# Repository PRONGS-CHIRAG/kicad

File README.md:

# KiCAD Mitos

Natural-language batch editing for KiCAD. You select components, describe the change in plain
language, review a structured action plan, approve it, and the change is executed, verified with
KiCAD's own ERC and automatically rolled back if it fails verification.

Supported connection patterns: **I2C**, **SPI**, **UART**, a single **GPIO** link and a
**power-only** hookup. A protocol is a data table of per-signal pin aliases, named separately
for the controller and the peripheral — which is how UART's TX/RX crossover falls out with no
special case. All of them decompose into the same three action types.

## How it works

```
read project -> plan (rules or LLM) -> preview + approve -> checkpoint
             -> execute -> re-read + ERC -> deterministic decision -> accept | restore
```

- The LLM (optional) only *proposes* structured actions. It never decides whether a change is accepted.
- The accept/reject decision is deterministic and based on the real project: expected connections,
  supporting components, protected objects, unauthorized changes and new critical ERC violations.
- ERC is compared violation-by-violation against a baseline, not by counting, so pre-existing
  violations are never blamed on the change and a "swapped" violation is still detected.
- DRC runs too when the project has a board, including KiCAD's schematic-parity check, and it is a
  real gate for any run that wrote the board — which a schematic edit does, because the board is
  synced to match. The one carve-out is unconnected items whose every net that sync touched: a synced
  board is unrouted by design, so those are pending work, not a regression. An unconnected item on any
  other net still rejects, so severed copper cannot slip through.
- The DRC baseline is the union of a couple of passes, because KiCAD's own DRC is not deterministic:
  on a byte-identical board it intermittently reports one or two fewer clearance violations. Whichever
  run became the baseline would otherwise decide whether a later, normal run looked like it introduced
  errors, which rejected valid work about one time in twenty.
- The file-level diff is snapshotted straight after execution, before ERC runs, because `kicad-cli`
  rewrites project files as a side effect. Only the schematic may change; a touched `.kicad_pro` or
  symbol library is an unauthorized change.
- Every run is transactional: the whole project is checkpointed and fully restored if any check fails.
- The UI shows the live schematic (and the board, for projects with a `.kicad_pcb`) rendered by
  `kicad-cli` from the session's working copy: `GET /api/sessions/{id}/render?view=schematic|pcb`.
  It renders what is on disk, so a proposed plan changes nothing until you approve it, and a rejected
  run is rolled back before the next render.

## Quick start with Docker (recommended)

`kicad-cli` is the source of truth for ERC/DRC, and the image ships it, so this is the only setup in
which the pipeline can actually accept a change.

```bash
docker compose up --build     # backend :8000, frontend :3000
```

The backend image build **fails** rather than starting degraded if `kicad-cli`, `sch erc` or `pcb drc`
are missing. It is based on Ubuntu 26.04, which packages KiCAD 9 for both amd64 and arm64; note that
`sch erc` / `pcb drc` only exist from KiCAD 8 onward (Ubuntu 24.04 ships KiCAD 7, whose CLI has export
subcommands only) and the KiCAD PPAs publish amd64 only.

## Layout

| Path | Purpose |
| --- | --- |
| `backend/app/kicad` | S-expression parsing, schematic reader/writer, ERC/DRC, checkpoints, state diff |
| `backend/app/planning` | Instruction parsing, deterministic planner, rule validator, optional LLM planner |
| `backend/app/execution` | Local executor and the Mitos MCP executor adapter |
| `backend/app/decision.py` | Deterministic accept/reject logic |
| `backend/app/workflow.py` | Session store and the checkpoint/execute/validate/restore pipeline |
| `backend/app/benchmark.py` | The 10 benchmark scenarios, JSON + HTML report |
| `backend/app/demo.py` | Demo artefacts: accepted run, rolled-back run, benchmark summary |
| `backend/app/probe_mitos.py` | Writes the Mitos capability matrix from a live MCP server |
| `frontend` | Next.js UI, two lanes on one project: one change (selection + instruction -> plan preview -> verdict) or the ten-agent team (brief -> live stage flow -> release) |
| `fixtures/projects` | Generated KiCAD projects used by tests and benchmarks |

## Running without Docker

```bash
# backend
cd backend
python3 -m venv .venv && .venv/bin/pip install -e ".[dev]"
.venv/bin/uvicorn app.main:app --reload --port 8000

# frontend
cd frontend && npm install && npm run dev   # http://localhost:3000
```

Requires `kicad-cli` from KiCAD 8 or later on `PATH` for ERC/DRC. Without it the pipeline still runs,
but the decision engine refuses to accept a change it could not verify — every run comes back as
`needs_user_review`. The UI says so in a banner rather than looking healthy.

## Configuration

| Variable | Default | Meaning |
| --- | --- | --- |
| `KICAD_MITOS_WORKSPACE` | `/tmp/kicad-mitos` | Session copies, checkpoints and uploaded projects |
| `KICAD_MITOS_PROJECTS_DIR` | `fixtures/projects` | Read-only project source; the UI offers these *plus* `$KICAD_MITOS_WORKSPACE/projects` |
| `KICAD_MITOS_KICAD_CLI` | `kicad-cli` | KiCAD CLI binary |
| `KICAD_MITOS_EXECUTOR` | `local` | `local` or `mitos` |
| `KICAD_MITOS_MITOS_COMMAND` | – | Command that starts the Mitos MCP server (stdio) |
| `KICAD_MITOS_CORS_ORIGINS` | `["http://localhost:3000"]` | JSON array of allowed browser origins |
| `OPENAI_API_KEY` | – | Enables LLM planning; falls back to the rule planner on any failure |
| `KICAD_MITOS_DEVIN_API_KEY` | – | Devin service-user key (`cog_…`); `DEVIN_API_KEY` also works |
| `KICAD_MITOS_AUTO_RESOLVE` | `false` | Let the Devin agent answer an ambiguity instead of asking you |
| `KICAD_MITOS_DEVIN_BASE_URL` | `https://api.devin.ai/v3` | Enterprise tenant override. `cog_` keys work only on v3 |
| `KICAD_MITOS_DEVIN_ORG_ID` | auto | Discovered from `GET /v3/self`; set only to pin one org |
| `KICAD_MITOS_DEVIN_MODE` | `normal` | `normal｜fast｜lite｜ultra｜fusion`; `fast` is ~2× quicker at ~4× ACU |
| `KICAD_MITOS_DEVIN_TIMEOUT_SECONDS` | `180` | Ceiling before falling back to asking |
| `KICAD_MITOS_DEVIN_POLL_SECONDS` | `5` | Poll interval while the session runs |
| `KICAD_MITOS_DEVIN_MAX_ACU` | `5` | ACU ceiling per session |

Copy `backend/.env.example` to `backend/.env` (git-ignored) and paste the key there, or export it in
the shell.

## The Devin agent: thinking instead of asking

By default the planner refuses to guess — no SDA pin named on the symbol means a question, not an
assumption. Set a Devin key **and** `KICAD_MITOS_AUTO_RESOLVE=true` and a *resolvable* ambiguity goes
to a Devin session instead, so planning continues on its own. The result is a mixture, and the split
is the point:

| | does |
| --- | --- |
| Devin agent | answers one missing detail, from the real pin table and the part's datasheet |
| Deterministic rules | build the plan, validate it, run ERC/DRC, decide, roll back |

The agent never writes an action, never sees the validator, and has no say in accept/reject. Every
answer it gives must be one of the options the planner itself offered — anything else is discarded —
and each one is recorded as a visible assumption on the plan, so the preview says *"3:P3 chosen … by
the Devin agent: the datasheet says pin 3 is SDA"* rather than presenting it as fact. `source` on the
plan response reads `agent+rules` when the agent contributed.

**Three clarifications are never auto-resolved**, because they are refusals rather than ambiguities:
`incompatible_voltage`, `incompatible_logic_voltage` and `unsupported_protocol`. Asking for 5 V must
not quietly become a 3.3 V bus (plan §21: better to reject an uncertain instruction than silently
produce a wrong connection). Neither are the three that pick *which* components get connected. The
resolvable set is an allowlist, so a reason code added later is unresolvable until someone says
otherwise.

If the session times out, errors, answers something that was not on the list, **or leads to a plan
the validator rejects**, the question comes back to you — the agent degrades to the old behaviour
rather than to a dead screen. That last case is not hypothetical: running this against the live API,
the agent picked a pin that the fixture ties to GND, which would have grounded the I2C clock. The
validator caught it (*"refusing to pull up power net GND"*), and the run fell back to asking. The
agent is fallible; the rules are the backstop, which is the whole point of the split.

Measured against the live v3 API: an answer arrives in roughly 20–40 s for 0 ACU, and it arrives
while the session is still `running` — the client reads `structured_output` the moment it appears
instead of waiting for the session to exit.

**This sends your schematic to a third party.** The prompt carries the selected components, their pin
tables and the project's net names to `api.devin.ai` so the agent can reason about the real design.
That data flow does not exist unless you set the key and the opt-in.

## Projects

The UI lists the bundled fixtures plus any project uploaded through it. Uploads are zip archives with
the `.kicad_sch` at the archive root; they are extracted into the server workspace
(`$KICAD_MITOS_WORKSPACE/projects`), never into the git-tracked fixtures, and the extractor rejects
absolute paths, `..` traversal, oversized archives and anything that is not a KiCAD project file.

## Planning: form or prose

Both entry points produce the same schema and run through the same validator:

- **Fields** — pick interface, logic voltage, SDA/SCL pins and pull-up value. Never calls the LLM.
- **Words** — the written instruction is parsed into the same fields.

## Tests and benchmarks

```bash
# with the real kicad-cli, via the image
docker compose run --rm --no-deps backend pytest -q
docker compose run --rm --no-deps backend python -m app.benchmark --out /workspace/reports
docker compose run --rm --no-deps backend python -m app.demo --out /workspace/reports/demo

# or locally
cd backend
.venv/bin/pytest -q
.venv/bin/python -m app.benchmark --out reports   # reports/benchmark.{json,html}
.venv/bin/python -m app.demo --out reports/demo   # index.html with before/after renders
```

`app.demo` builds the three demo artefacts from §28 of the plan: an accepted batch, a batch that is
rejected and restored, and the benchmark table. The rejected run needs a fault to reject and no
instruction produces one organically (a wrong-voltage request is caught at planning time, before
anything executes), so it injects a deliberately broken executor — labelled as an injected fault in
both the JSON and the HTML.

The benchmark covers the ten scenarios from the product plan: standard connection, existing
pull-ups, missing pin names, wrong voltage, protected USB circuit, pre-existing ERC warnings,
a deliberately wrong connection, partial execution failure, unknown component and an ambiguous
instruction.

## Mitos integration

`backend/app/execution/mitos.py` speaks MCP over stdio and forwards only validated actions, and
`backend/app/mcp_server.py` is a real MCP server implementing the four tools it calls. So the MCP
path is not decorative — it runs the whole pipeline for real:

```bash
KICAD_MITOS_EXECUTOR=mitos KICAD_MITOS_MITOS_COMMAND="python3 -m app.mcp_server" \
  python -m app.benchmark --out reports        # 10/10, every edit over JSON-RPC
```

Both executors call the same edit primitives (`app/kicad/edits.py`), so the local and MCP paths
cannot drift: driving the golden plan through either leaves byte-identical pin-to-net state, and a
tool failure mid-batch still rolls the whole project back, hash-verified.

What this does *not* claim: the third-party Mitos server is still unconfirmed — nothing reachable
here speaks for it, and searching turns up no public Mitos. `DEFAULT_TOOL_MAP` is configurable
precisely so its real names can be dropped in. See `docs/mitos.md`, which is generated from a live
`tools/list` and says which server it was generated from.

## Ten-agent engineering team

The team coordinates a project manager, requirements, architecture, component, schematic, PCB
layout, simulation, verification, manufacturing, and QA/release agent. The canonical workflow runs
layout and simulation as siblings, then verifies, checks manufacturing, and prepares release.
Failed gates route to the responsible stage and replay the downstream remainder; two return trips end
in human review.

Agents receive parsed schematic and board context. Devin runs use validated structured output and
one session per invocation. Keyless runs use the explicitly labelled `STUB` runner, which is
deterministic and never contacts Devin. Agents do not edit files or open pull requests; schematic
and placement proposals are applied only through checkpointed, deterministic gates.

The UI carries the team as its own lane: pick a project, switch to **Ten-agent team**, brief it, and
the run is drawn stage by stage as it executes — each agent, the deterministic gate that has to accept
its output, the fork where layout and simulation overlap, every return trip, and the release verdict.
Live progress is read from the append-only evidence the orchestrator writes as it goes, so what is on
screen is what the run recorded. The single exception is which stage is drawn as *working*: an agent
appends its record only once it finishes, so the stage in flight is inferred as the canonical successor
of the last gate that passed — and after a gate *fails* no stage claims to be working at all, because
which agent picks the work up is decided by the finding text inside the backend. The lane
picks the offline `STUB` runner by default; choosing `devin` opens real sessions and says so next to
the button. A run that ends in `needs_human_review` can be answered from that panel, which appends the
answer to the request and re-runs.

The background API provides `POST /api/team/runs` and status, report, evidence, and answer endpoints
at `/api/team/runs/{run_id}`, `/report`, `/evidence`, and `/answer`. A run reports the `session_id` of
the working copy it edits, so the UI renders the very files the schematic and layout stages write.
The equivalent CLI is:

```text
python -m app.team.cli --project fixtures/projects/esp32_i2c_demo \
  "Create and validate a small ESP32 temperature-monitoring PCB with an I²C sensor and USB-C power."
```

Evidence is append-only under `settings.workspace_dir/team/<run_id>/`, including stage outputs,
gate results, events, checkpoints, and artifacts. The current MVP does not route copper or run
ngspice; simulation is closed-form arithmetic, and footprint extents are checked only where the
parser exposes them. `ready for engineering review` is not a guarantee that a board works: KiCAD
checks cannot replace physical prototyping and lab validation.

Point the probe at a running server and it writes the capability matrix from what the server actually
advertises, including each tool's input schema:

```bash
python -m app.probe_mitos --command "<command that starts the Mitos MCP server>"
```

It exits non-zero and writes nothing when no server answers, so an unverified matrix can never
masquerade as a verified one. The adapter itself is covered by tests that run it against
`backend/tests/mitos_stub.py`, a stdio MCP test double — those prove the client, the action-to-tool
mapping and the probe work, and prove nothing about the real Mitos server.

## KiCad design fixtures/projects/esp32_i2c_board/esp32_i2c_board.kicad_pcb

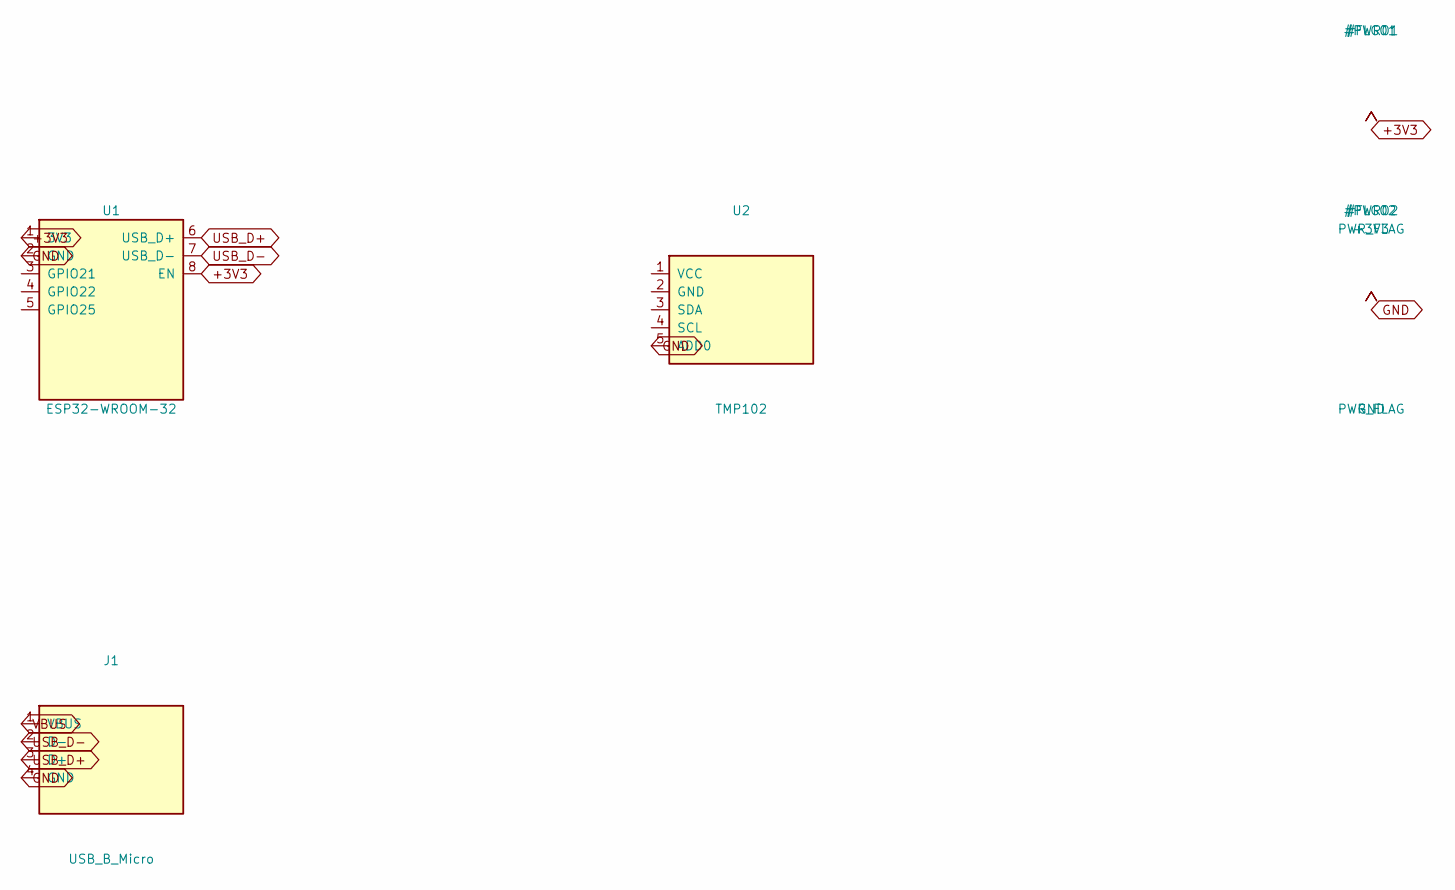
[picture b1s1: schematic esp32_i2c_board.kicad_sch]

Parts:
J1: USB_B_Micro
U1: ESP32-WROOM-32
U2: TMP102

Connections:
+3V3: U1.1 (3V3), U1.8 (EN)
GND: J1.4 (GND), U1.2 (GND), U2.5 (ADD0)
USB_D+: J1.3 (D+), U1.6 (USB_D+)
USB_D-: J1.2 (D-), U1.7 (USB_D-)
VBUS: J1.1 (VBUS)

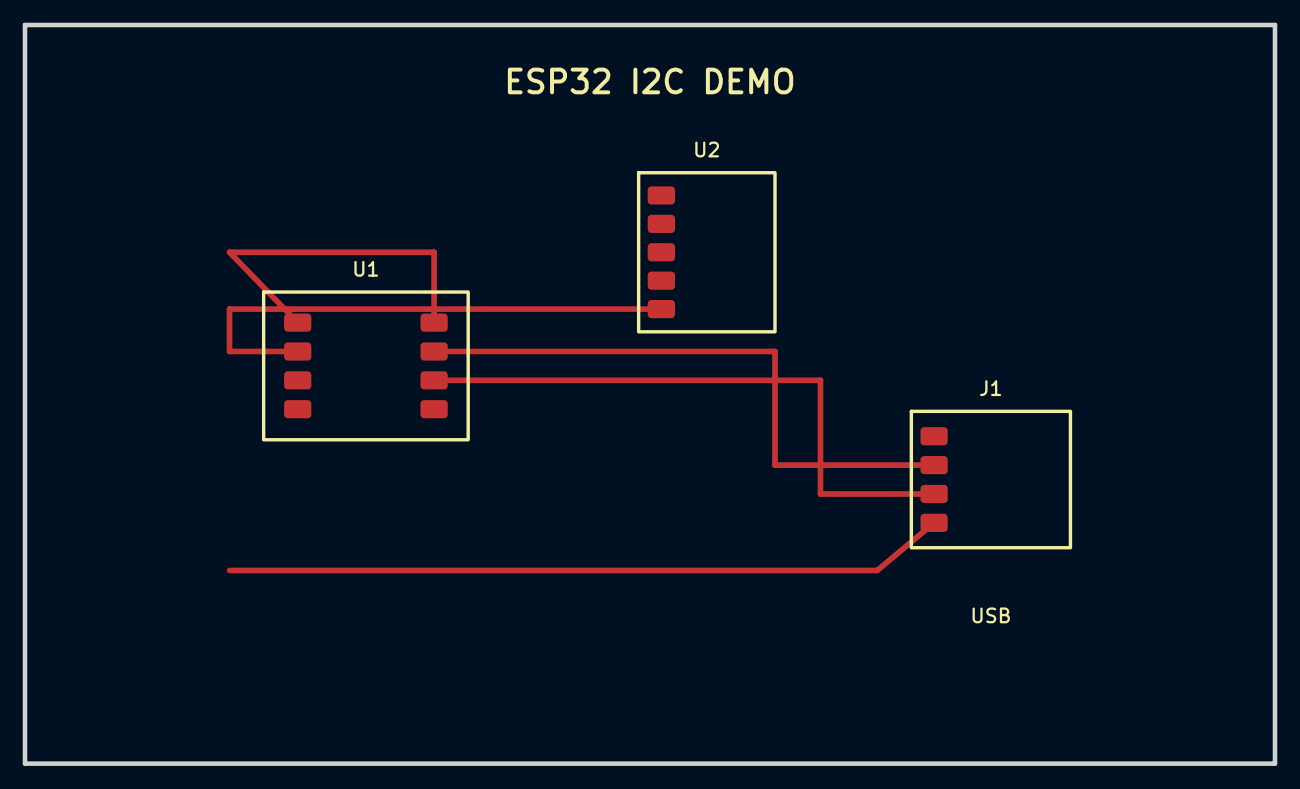
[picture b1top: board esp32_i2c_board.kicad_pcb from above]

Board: 2 copper layers, 110.0 x 65.0 mm, 3 parts (0 on the bottom side), 4 nets.
